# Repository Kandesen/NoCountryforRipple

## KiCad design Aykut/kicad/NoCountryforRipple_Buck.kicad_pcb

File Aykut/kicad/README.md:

# KiCad project: 60 W synchronous buck (LTC7801)

Open `NoCountryforRipple_Buck.kicad_pro` in KiCad 10. The files were generated with KiCad 7.0 tools, and KiCad 10 upgrades them when you save.

| File | Content |
|---|---|
| `NoCountryforRipple_Buck.kicad_sch` | Schematic (one A3 sheet): input + add-on 1, power stage, controller, add-on 2 |
| `NoCountryforRipple_Buck.kicad_pcb` | 4-layer PCB, 78 × 62 mm, fully routed |
| `lib/NCFR.kicad_sym` | Project symbols: `LTC7801` and `TLV431_DBZ` |
| `lib/NCFR.pretty/LTC7801_FE24_AA.kicad_mod` | LTC7801 TSSOP-24 footprint with exposed pad (FE24 AA: EP 2.74 × 3.25 mm, 6 thermal vias) |
| `bom/BOM_NoCountryforRipple_Buck.csv` | BOM grouped by MPN, with fit status, supplier to order from (EKOM / Özdisan / Mouser), stock and prices at each, and Digi-Key/Mouser search links |
| `docs/` | Schematic PDF, layer plots and `assembly_top.pdf` (part outlines with every reference, A4, for hand assembly) |

## Symbol fields
Every part has `MPN`, `Manufacturer` and `Fit`. `Fit` is one of: Base, Add-on 1 (reverse polarity), Add-on 2 (current limit), or a DNP option. DNP parts carry KiCad's *Do not populate* flag.
- **Removing add-on 1:** leave Q3, R1 and D1 unpopulated and fit JP1 (a 0 Ω 2512 resistor or a wire).
- **Removing add-on 2:** leave every part in the add-on 2 box unpopulated (U2–U4, D2, R15, R20–R28, C23, C25–C28, TP13).

## Board
- **Stack-up:** F.Cu (power copper + parts), In1.Cu (solid GND), In2.Cu (signals + GND fill), B.Cu (signals + GND fill). Standard 1.6 mm, 1 oz outer layers.
- **Rules:** minimum clearance 0.2 mm, minimum track 0.2 mm, vias 0.6/0.3 mm, 0.5 mm to the board edge. Every part is on the top side; there is no stencil, so paste is applied with the dispenser.
- **Power copper (F.Cu zones):** VIN, VIN_N (reverse-polarity FET), SW, SNSP (L1 → R5) and VOUT. The six input ceramics sit on the VIN/GND boundary directly above Q1 and Q2 (hot loop about 10 × 8 mm over the solid In1 GND).
- **Current sense:** Kelvin traces from inside the R5 pads run on In2 to R6/R7 (LTC7801 SENSE± filter) and on B.Cu to U2 (INA180).
- **Gate drive:** U1 → R2/R3 (0 Ω, change to a few Ω to slow the edges) → vias next to the Q1/Q2 gate pads. R2 sits directly above the gate-driver pins and R3 on the direct line towards Q2; test points TP4 (TG) and TP5 (BG) are next to them. Controller pin to MOSFET gate: TG about 29 mm (the straight line is 22 mm, because Q1 is at the far end of the power stage), BG about 21 mm. The TG track runs on In2 next to its SW return for most of its length. D3 (optional bootstrap diode, not fitted) was moved above the controller to make room for R3.
- **DRC (KiCad 7):** no clearance errors, no unconnected items. No silkscreen overlaps. The only remaining items are "library footprint" notices that only appear because the generator did not have your library paths.

## Sourcing
- **Supplier order:** e-komponent.com (EKOM, Digi-Key's distributor in Turkey) and Özdisan first; Digi-Key or Mouser (mouser.com.tr) only for parts neither of them stocks. Rule per BOM line: the exact part at EKOM → EKOM; otherwise the exact part at Özdisan → Özdisan; otherwise an equivalent (same footprint, pinout and rating) at EKOM/Özdisan; otherwise Mouser/Digi-Key. The BOM's "Order from / Order part" columns apply this; the EKOM, Özdisan and Mouser/Digi-Key columns list what each one had on **22 Nov 2026**.
- **EKOM:** most of its stock is Digi-Key stock shipped from abroad (7–10 working days, estimated dispatch 1–7 Dec 2026); the price includes shipping and customs. Only R25 (RC0805FR-0730K1L) was in stock in Turkey (1–3 days). Prices in the BOM are EKOM's 1-piece USD price without the 20 % VAT (the TL price on the site includes VAT).
- **What the BOM orders:** every part, including the ones not fitted by default (D3, JP1, R4, C13, R11), plus a limited set of spares that keeps the order under the 100 USD budget. "Qty per board" is the fitted quantity, "Spares" the extra pieces and "Qty to order" their sum.
- **Spares and why:** one LTC7801 (hardest part to hand-solder without a stencil, longest lead time); one BSC117N08NS5 (Q1/Q2 are the most likely to fail during bring-up); one LM2904B and one 1N4148W (cheap); one of every 0805 resistor and capacitor in a fitted position, once per part number (easily lost when hand-soldering). No spares for L1, R5, the 1206/1210 capacitors, C1, C10, Q3, U2, U4 or the parts not fitted by default.
- **Cost of the order (single-unit prices, USD excl. VAT):** base 61.6, add-on 1 4.1, add-on 2 5.5, parts not fitted by default 1.7, spares 22.7, total about 95.6. By supplier: EKOM 61.6, Özdisan 2.8 (estimated with Mouser prices; Royalohm resistors are sold in 100s), Mouser 31.2. Quantity breaks make the real total a little lower, but EKOM's USD prices follow the exchange rate, so recheck the total on the order day.
- **Every MPN in the schematic and BOM is the part that is ordered** (the "Order part" column says "same part" on every line). To get there, these design parts were replaced on 22 Nov 2026 by equivalents that EKOM/Özdisan stock (same footprint, pinout and rating):
  - C10: KEMET A768EB107M1ELAS036 (100 µF 25 V polymer, 6.3 mm can, 36 mΩ, 1.26 A ripple) instead of Panasonic EEH-ZA1E101XP.
  - C15: KEMET C0805C104K1RACTU; C20: KEMET C0805C682K5RACTU (instead of Yageo CC0805 parts).
  - U2: INA180A1IDBVT (same IC, industrial grade) instead of INA180A1QDBVRQ1. U4: TLV431BCDBZR (0–70 °C grade, same accuracy and pinout) instead of TLV431BIDBZR. D1: Taiwan Semiconductor BZT52C12-G RHG (12 V, 5 %) instead of Comchip BZT52B12-HF.
  - J1/J2 plug: Phoenix 1765551 (MSTB 2,5/2-ST-5,08 AU, same series) instead of 1757019, which EKOM only quotes. The header 1757242 is unchanged.
  - R14: Royalohm 0805S8F2372T5E from Özdisan (sold in 100s) instead of Yageo RC0805FR-0723K7L. R4 (not fitted): Yageo RC1206JR-072R2L (5 %) instead of the 1 % part.
- **Alternative R28 values** (not fitted, two of each): 2.37 kΩ (7.94 A, EKOM), 2.32 kΩ (7.80 A, Özdisan), 2.26 kΩ (7.64 A, Özdisan), 2.21 kΩ (7.50 A, EKOM) and 1.54 kΩ (5.53 A, Özdisan; the standard 5 A design if the overload bonus is dropped). R28 = 2.49 kΩ (8.26 A) is fitted for the first power-up so that 12 V / 7.5 A is always supplied in regulation, even with worst-case tolerances (about ±6 %). After the real limit has been measured on the bench, R28 is swapped to bring the limit to about 7.6 A (2 % above the 7.5 A target).
- **From Mouser (mouser.com.tr):** U1 LTC7801EFE#PBF × 2 (EKOM lists only the LTC7801IFE#PBF, on request; Mouser Türkiye had 1,587), R12 1.02 MΩ, D3 BAT46ZFILM (no BAT46 in stock at EKOM) and JP1 CRF2512-J/-000ELF.
- **L1 (Würth 74435582200):** EKOM 101 (Digi-Key stock), 9.18 USD; Mouser 0 (3,543 due 11 Dec 2026). Order it first.
- **Parts not fitted by default** are ordered too: R4, C13 and R11 (EKOM), D3 and JP1 (Mouser). EKOM's Bourns CRF2512-JZ-R005ELF (5 mΩ metal strip) would also work for JP1 (48 mW at 3.1 A).
- Earlier swaps re-checked at EKOM: Murata GRM32ER72A225KA35L, Samsung CL32B226KAJNNNE / CL31B106KAHNNNE / CL21B104KCFNNNE and BAT46W-7-F are out of stock there; Yageo RC2512JK-070RL is stocked but rated 2 A (too low for JP1); INA180B1IDBVR is stocked but has the other pinout. None of the earlier swaps needs to be undone.

## What has been verified
- **Schematic ↔ intended design:** KiCad's exported netlist was compared pin by pin with the intended netlist (191 pins, no differences). The intended netlist was reviewed net by net against the design.
- **Pinouts checked against datasheets:**
  - LTC7801 FE24: pin table; exposed pad = GND.
  - INA180A1 (pinout A): OUT 1, GND 2, IN+ 3, IN− 4, VS 5.
  - TLV431 DBZ: 1 REF, 2 K, 3 A (custom symbol).
  - BSC117N08NS5 / BSC030N08NS5 (TDSON-8): 1–3 S, 4 G, 5 D.
  - Polarity of the polymer capacitors C1 and C10.
- **Simulation ↔ schematic:** the LTspice files in `sim/ltspice/` use the same reference designators and values as this schematic (lumped parts: C2_12 = C2–C5, C11, C12; C6_9 = C6–C9). The report figures and the BOM notes use the same names; RB/RA/RS/RC/CC/CC2 in the report's equations are R8/R9/R5/R16/C20/C21.
- **Board ↔ schematic:** every footprint is linked to its symbol, and all pad nets match the netlist (no differences).
- **DRC (KiCad 7.0.11):** no clearance errors, no unconnected items.
- **Copper continuity:** the VIN, VIN_N, SW, SNSP and VOUT copper each fill as one island. In1, In2 and B.Cu GND are each one island.
- **Kelvin sensing:** the sense traces from inside the R5 pads connect only to R6/R7 and U2. No other VOUT/SNSP copper touches them, so no load current flows in the sense lines.
- **Cost:** about 71 USD (excl. VAT) for one fully populated board (base 61.6, add-on 1 4.1, add-on 2 5.5); about 95.6 USD for the whole order with the parts not fitted by default and the spares. See the BOM totals.

## Known points to improve or check interactively
- **Gate drive and ringing:** the gate paths were shortened on 22 Nov (TG about 34 → 29 mm, BG 28 → 21 mm). If the switch node rings too much on the bench (TP3, 48 V, full load), first increase R2/R3 to 2.2–4.7 Ω, then fit the R4/C13 snubber (2.2 Ω, 330 pF C0G; R4 dissipates about 0.15 W at 48 V).
- **Decoupling at U1:** C16 (DRVCC, 10 µF) now sits left of the controller with about 4 mm of track to pins 17/18 (was about 10 mm), and C15 (VIN, 100 nF) about 4 mm from pin 19 (was 7.6 mm). Moved on 22 Nov; DRC clean.
- **Silkscreen:** every label is placed clear of pads and other labels. Six small parts next to the controller (C15, C19, C20, C21, C28, R19) had no free space for a label, so their labels are hidden on the board; `docs/assembly_top.pdf` shows all references.
- **Vias in the R5 pads:** the Kelvin vias sit inside R5's pads, so a little solder may wick into them. Use enough paste on R5.

## Before ordering (in KiCad 10)
1. Run ERC on the schematic. KiCad 7's command line has no ERC, so connectivity was checked instead by comparing the exported netlist pin by pin with the intended netlist.
2. Run *Tools → Update PCB from Schematic*. Nothing should change, because the footprints are linked to their symbols.
3. Refill zones (B), run DRC, and look at the 3D view.
4. Check the LTC7801 footprint against the datasheet's FE24(AA) drawing (exposed-pad size), and that the 5.08 mm header faces outward.
5. Ask the PCB manufacturer for its 4-layer stack-up and minimum rules (most allow 0.15 mm / 0.3 mm drill), then plot the Gerbers and drill files.

## Report names → KiCad designators
| Report | KiCad | | Report | KiCad |
|---|---|---|---|---|
| R_S (6 mΩ sense) | R5 | | R_SS (330 k) | R15 |
| R_A / R_B (feedback) | R9 / R8 | | R_inj (22 k) | R23 |
| R_C / C_C / C_C2 (ITH) | R16 / C20 / C21 | | R_i / C_i (integrator) | R22 / C26 |
| C_SS | C19 | | R_2 / C_2 (integrator input) | R21 / C25 |
| R_FREQ / R_DRVSET | R17 / R18 | | UVLO divider | R12, R13, R14 |
| Input ceramics | C2–C5, C11, C12 | | Output ceramics / polymer | C6–C9 / C10 |

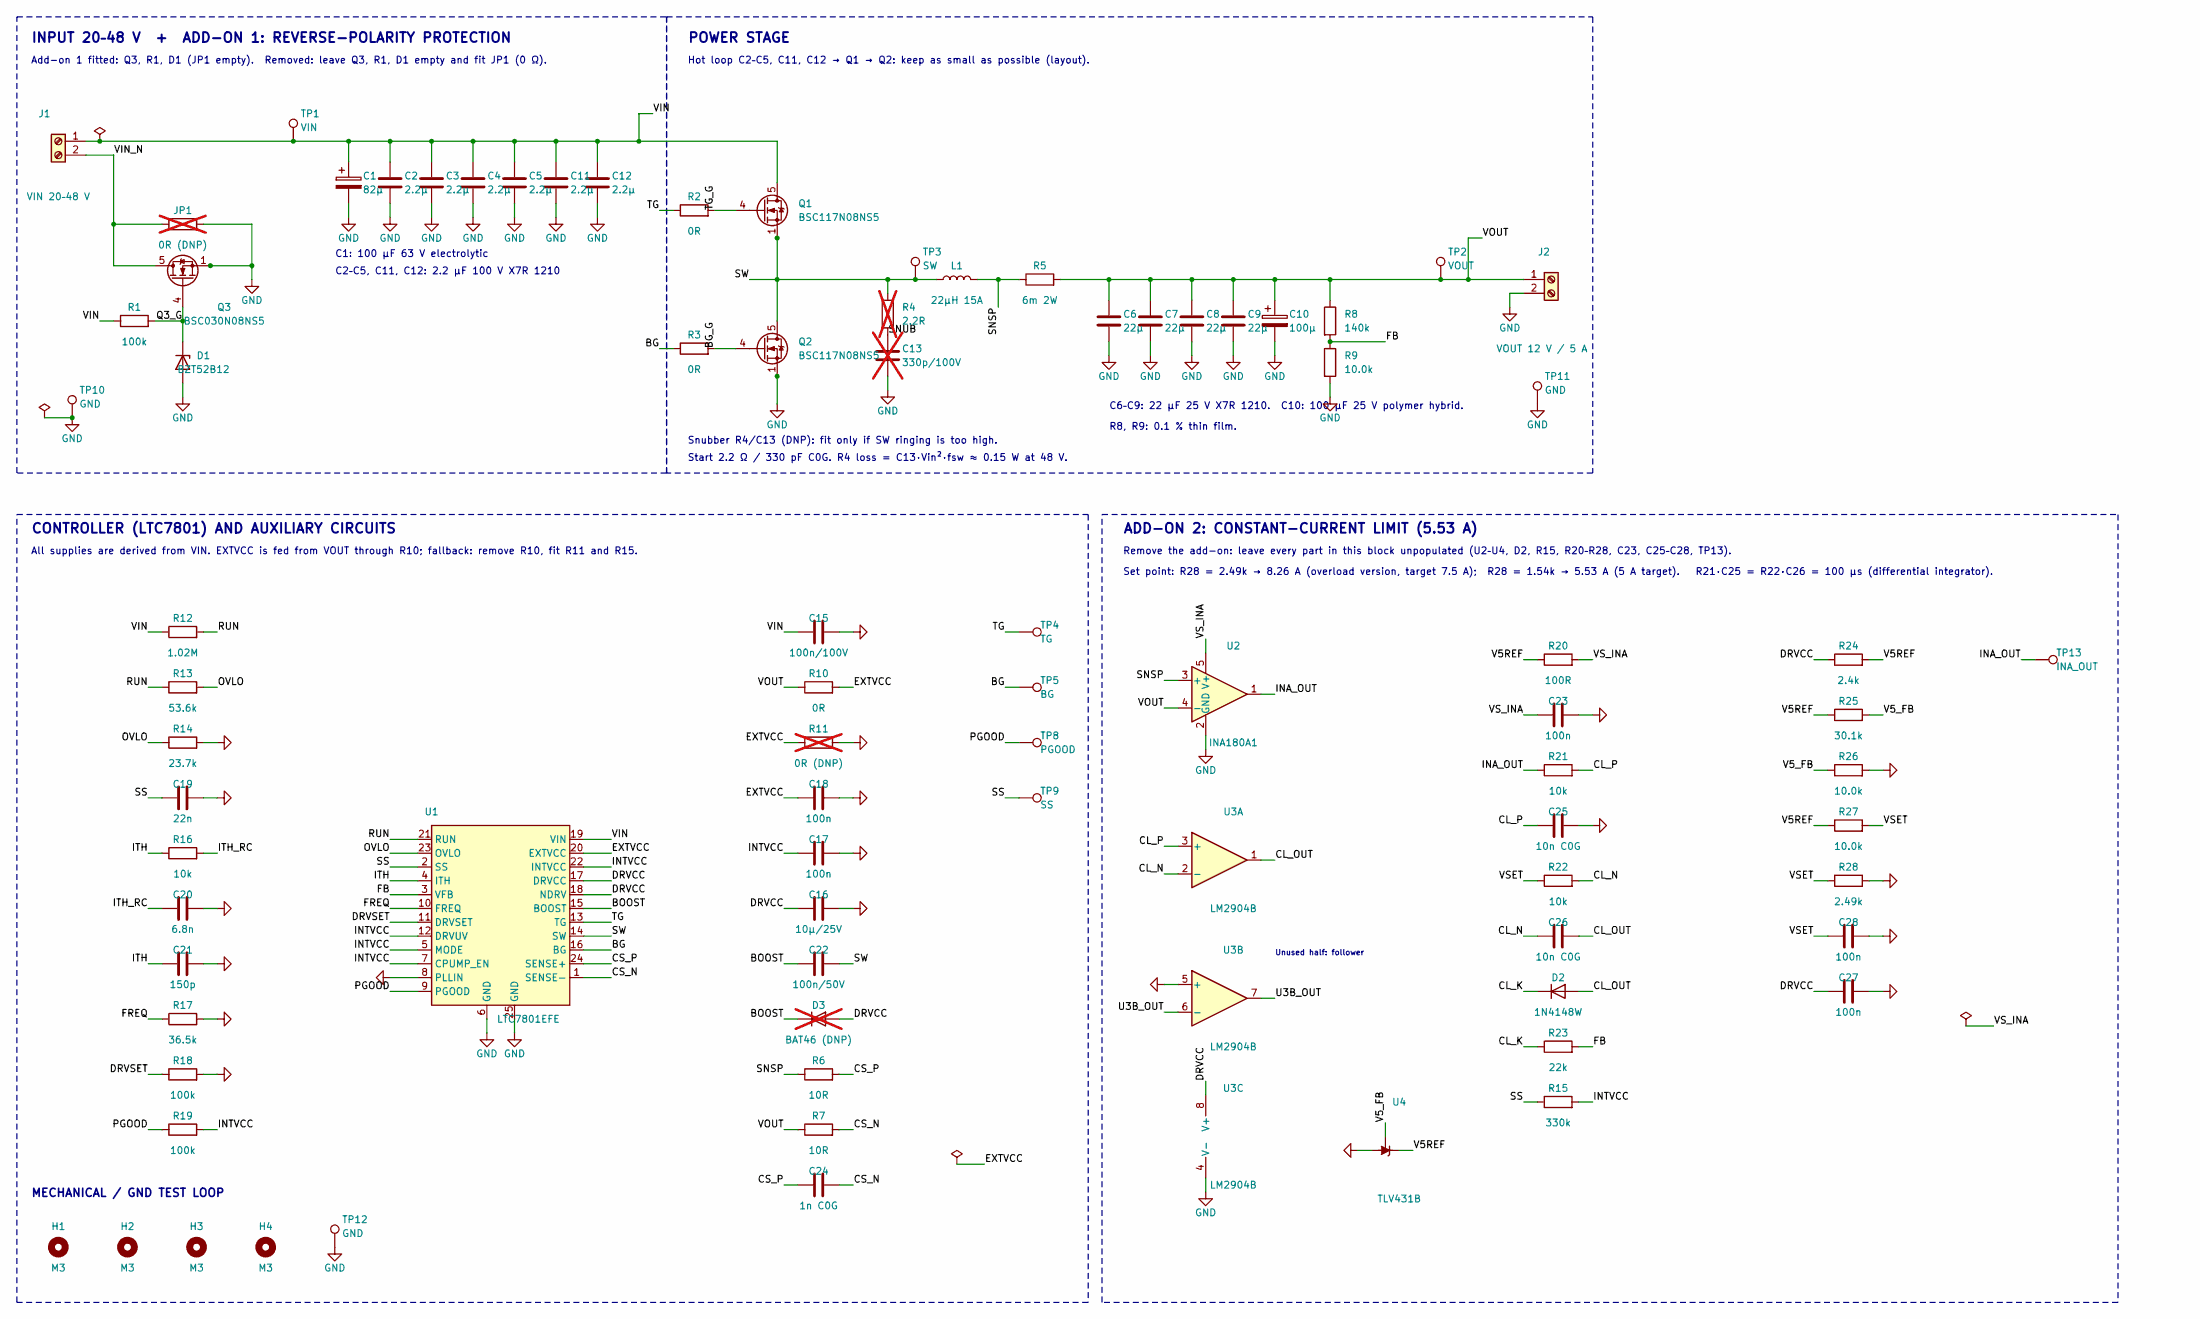
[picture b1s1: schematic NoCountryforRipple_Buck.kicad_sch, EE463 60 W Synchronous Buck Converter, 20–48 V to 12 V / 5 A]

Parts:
C1: 82µ; CP_Elec_10x10; Voltage 63 V; MPN A786MN826M1JLAS018
C2, C3, C4, C5, C11, C12: 2.2µ; C_1210_3225Metric; Voltage 100 V; MPN C1210C225K1RACTU
C6, C7, C8, C9: 22µ; C_1210_3225Metric; Voltage 25 V; MPN C3225X7R1E226M250AB
C10: 100µ; CP_Elec_6.3x7.7; Voltage 25 V; MPN EEH-ZA1E101XP
C13: 330p/100V; C_0805_2012Metric; MPN C0805C331J1GACTU; not fitted
C15: 100n/100V; C_0805_2012Metric; MPN CC0805KKX7R0BB104
C16: 10µ/25V; C_1206_3216Metric; MPN CC1206KKX7R8BB106
C17, C18, C23, C27, C28: 100n; C_0805_2012Metric; MPN CL21B104KBCNNNC
C19: 22n; C_0805_2012Metric; MPN CL21B223KBANNNC
C20: 6.8n; C_0805_2012Metric; MPN CC0805KRX7R9BB682
C21: 150p; C_0805_2012Metric; MPN CC0805JRNPO9BN151
C22: 100n/50V; C_0805_2012Metric; MPN CL21B104KBCNNNC
C24: 1n C0G; C_0805_2012Metric; MPN CC0805JRNPO9BN102
C25, C26: 10n C0G; C_0805_2012Metric; MPN CL21C103JBFNNNE
D1: BZT52B12; D_SOD-123; MPN BZT52B12-HF
D2: 1N4148W; D_SOD-123; MPN 1N4148W-7-F
D3: BAT46 (DNP); D_SOD-123; MPN BAT46ZFILM; not fitted
H1, H2, H3, H4: M3; MountingHole_3.2mm_M3; MPN —
J1: VIN 20–48 V; PhoenixContact_MSTBA_2,5_2-G-5,08_1x02_P5.08mm_Horizontal; MPN 1757242 + plug 1757019
J2: VOUT 12 V / 5 A; PhoenixContact_MSTBA_2,5_2-G-5,08_1x02_P5.08mm_Horizontal; MPN 1757242 + plug 1757019
JP1: 0R (DNP); R_2512_6332Metric; MPN CRF2512-J/-000ELF; not fitted
L1: 22µH 15A; L_Wuerth_HCI-2212; MPN 74435582200
Q1, Q2: BSC117N08NS5; TDSON-8-1; MPN BSC117N08NS5ATMA1
Q3: BSC030N08NS5; TDSON-8-1; MPN BSC030N08NS5ATMA1
R1, R18, R19: 100k; R_0805_2012Metric; MPN RC0805FR-07100KL
R2, R3, R10: 0R; R_0805_2012Metric; MPN RC0805JR-070RL
R4: 2.2R; R_1206_3216Metric; MPN RC1206FR-072R2L; not fitted
R5: 6m 2W; R_2512_6332Metric; MPN PA2512FKF7W0R006E
R6, R7: 10R; R_0805_2012Metric; MPN RC0805FR-0710RL
R8: 140k; R_0805_2012Metric; MPN RT0805BRD07140KL
R9: 10.0k; R_0805_2012Metric; MPN RT0805BRD0710KL
R11: 0R (DNP); R_0805_2012Metric; MPN RC0805JR-070RL; not fitted
R12: 1.02M; R_0805_2012Metric; MPN RC0805FR-071M02L
R13: 53.6k; R_0805_2012Metric; MPN RC0805FR-0753K6L
R14: 23.7k; R_0805_2012Metric; MPN RC0805FR-0723K7L
R15: 330k; R_0805_2012Metric; MPN RC0805FR-07330KL
R16, R21, R22: 10k; R_0805_2012Metric; MPN RC0805FR-0710KL
R17: 36.5k; R_0805_2012Metric; MPN RC0805FR-0736K5L
R20: 100R; R_0805_2012Metric; MPN RC0805FR-07100RL
R23: 22k; R_0805_2012Metric; MPN RC0805FR-0722KL
R24: 2.4k; R_0805_2012Metric; MPN RC0805FR-072K4L
R25: 30.1k; R_0805_2012Metric; MPN RC0805FR-0730K1L
R26, R27: 10.0k; R_0805_2012Metric; MPN RC0805FR-0710KL
R28: 2.49k; R_0805_2012Metric; MPN RC0805FR-072K49L
TP1: VIN; TestPoint_Pad_D2.0mm; MPN —
TP2: VOUT; TestPoint_Pad_D2.0mm; MPN —
TP3: SW; TestPoint_Pad_D1.5mm; MPN —
TP4: TG; TestPoint_Pad_D1.5mm; MPN —
TP5: BG; TestPoint_Pad_D1.5mm; MPN —
TP8: PGOOD; TestPoint_Pad_D1.5mm; MPN —
TP9: SS; TestPoint_Pad_D1.5mm; MPN —
TP10, TP11, TP12: GND; TestPoint_Loop_D2.50mm_Drill1.0mm; MPN —
TP13: INA_OUT; TestPoint_Pad_D1.5mm; MPN —
U1: LTC7801EFE; LTC7801_FE24_AA; MPN LTC7801EFE#PBF
U2: INA180A1; SOT-23-5; MPN INA180A1QDBVRQ1
U3: LM2904B; SOIC-8_3.9x4.9mm_P1.27mm; MPN LM2904BIDR
U4: TLV431B; SOT-23; MPN TLV431BIDBZR

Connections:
BG: R3.1, TP5.1, U1.16 (BG)
BG_G: Q2.4 (G), R3.2
BOOST: C22.1, D3.1 (K), U1.15 (BOOST)
CL_K: D2.1 (K), R23.1
CL_N: C26.1, R22.2, U3.2 (-)
CL_OUT: C26.2, D2.2 (A), U3.1
CL_P: C25.1, R21.2, U3.3 (+)
CS_N: C24.2, R7.2, U1.1 (SENSE-)
CS_P: C24.1, R6.2, U1.24 (SENSE+)
DRVCC: C16.1, C27.1, D3.2 (A), R24.1, U1.17 (DRVCC), U1.18 (NDRV), U3.8 (V+)
DRVSET: R18.1, U1.11 (DRVSET)
EXTVCC: C18.1, R10.2, R11.1, U1.20 (EXTVCC)
FB: R8.2, R9.1, R23.2, U1.3 (VFB)
FREQ: R17.1, U1.10 (FREQ)
GND: C1.2, C2.2, C3.2, C4.2, C5.2, C6.2, C7.2, C8.2, C9.2, C10.2, C11.2, C12.2, C13.2, C15.2, C16.2, C17.2, C18.2, C19.2, C20.2, C21.2, C23.2, C25.2, C27.2, C28.2, D1.2 (A), J2.2, JP1.2, Q2.1 (S), Q2.2 (S), Q2.3 (S), Q3.1 (S), Q3.2 (S), Q3.3 (S), R9.2, R11.2, R14.2, R17.2, R18.2, R26.2, R28.2, TP10.1, TP11.1, TP12.1, U1.6 (GND), U1.8 (PLLIN), U1.25 (GND), U2.2 (GND), U3.4 (V-), U3.5 (+), U4.3 (A)
INA_OUT: R21.1, TP13.1, U2.1
INTVCC: C17.1, R15.2, R19.2, U1.5 (MODE), U1.7 (CPUMP_EN), U1.12 (DRVUV), U1.22 (INTVCC)
ITH: C21.1, R16.1, U1.4 (ITH)
ITH_RC: C20.1, R16.2
OVLO: R13.2, R14.1, U1.23 (OVLO)
PGOOD: R19.1, TP8.1, U1.9 (PGOOD)
Q3_G: D1.1 (K), Q3.4 (G), R1.2
RUN: R12.2, R13.1, U1.21 (RUN)
SNSP: L1.2, R5.1, R6.1, U2.3 (+)
SNUB: C13.1, R4.2
SS: C19.1, R15.1, TP9.1, U1.2 (SS)
SW: C22.2, L1.1, Q1.1 (S), Q1.2 (S), Q1.3 (S), Q2.5 (D), R4.1, TP3.1, U1.14 (SW)
TG: R2.1, TP4.1, U1.13 (TG)
TG_G: Q1.4 (G), R2.2
U3B_OUT: U3.6 (-), U3.7
V5REF: R20.1, R24.2, R25.1, R27.1, U4.2 (K)
V5_FB: R25.2, R26.1, U4.1 (REF)
VIN: C1.1, C2.1, C3.1, C4.1, C5.1, C11.1, C12.1, C15.1, J1.1, Q1.5 (D), R1.1, R12.1, TP1.1, U1.19 (VIN)
VIN_N: J1.2, JP1.1, Q3.5 (D)
VOUT: C6.1, C7.1, C8.1, C9.1, C10.1, J2.1, R5.2, R7.1, R8.1, R10.1, TP2.1, U2.4 (-)
VSET: C28.1, R22.1, R27.2, R28.1
VS_INA: C23.1, R20.2, U2.5 (V+)

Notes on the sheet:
INPUT 20–48 V + ADD-ON 1: REVERSE-POLARITY PROTECTION
Add-on 1 fitted: Q3, R1, D1 (JP1 empty). Removed: leave Q3, R1, D1 empty and fit JP1 (0 Ω).
C1: 100 µF 63 V electrolytic
C2–C5, C11, C12: 2.2 µF 100 V X7R 1210
Snubber R4/C13 (DNP): fit only if SW ringing is too high.
Start 2.2 Ω / 330 pF C0G. R4 loss = C13·Vin²·fsw ≈ 0.15 W at 48 V.
POWER STAGE
Hot loop C2–C5, C11, C12 → Q1 → Q2: keep as small as possible (layout).
C6–C9: 22 µF 25 V X7R 1210. C10: 100 µF 25 V polymer hybrid.
R8, R9: 0.1 % thin film.
CONTROLLER (LTC7801) AND AUXILIARY CIRCUITS
All supplies are derived from VIN. EXTVCC is fed from VOUT through R10; fallback: remove R10, fit R11 and R15.
ADD-ON 2: CONSTANT-CURRENT LIMIT (5.53 A)
Remove the add-on: leave every part in this block unpopulated (U2–U4, D2, R15, R20–R28, C23, C25–C28, TP13).
Set point: R28 = 2.49k → 8.26 A (overload version, target 7.5 A); R28 = 1.54k → 5.53 A (5 A target). R21·C25 = R22·C26 = 100 µs (differential integrator).
Unused half: follower
MECHANICAL / GND TEST LOOP

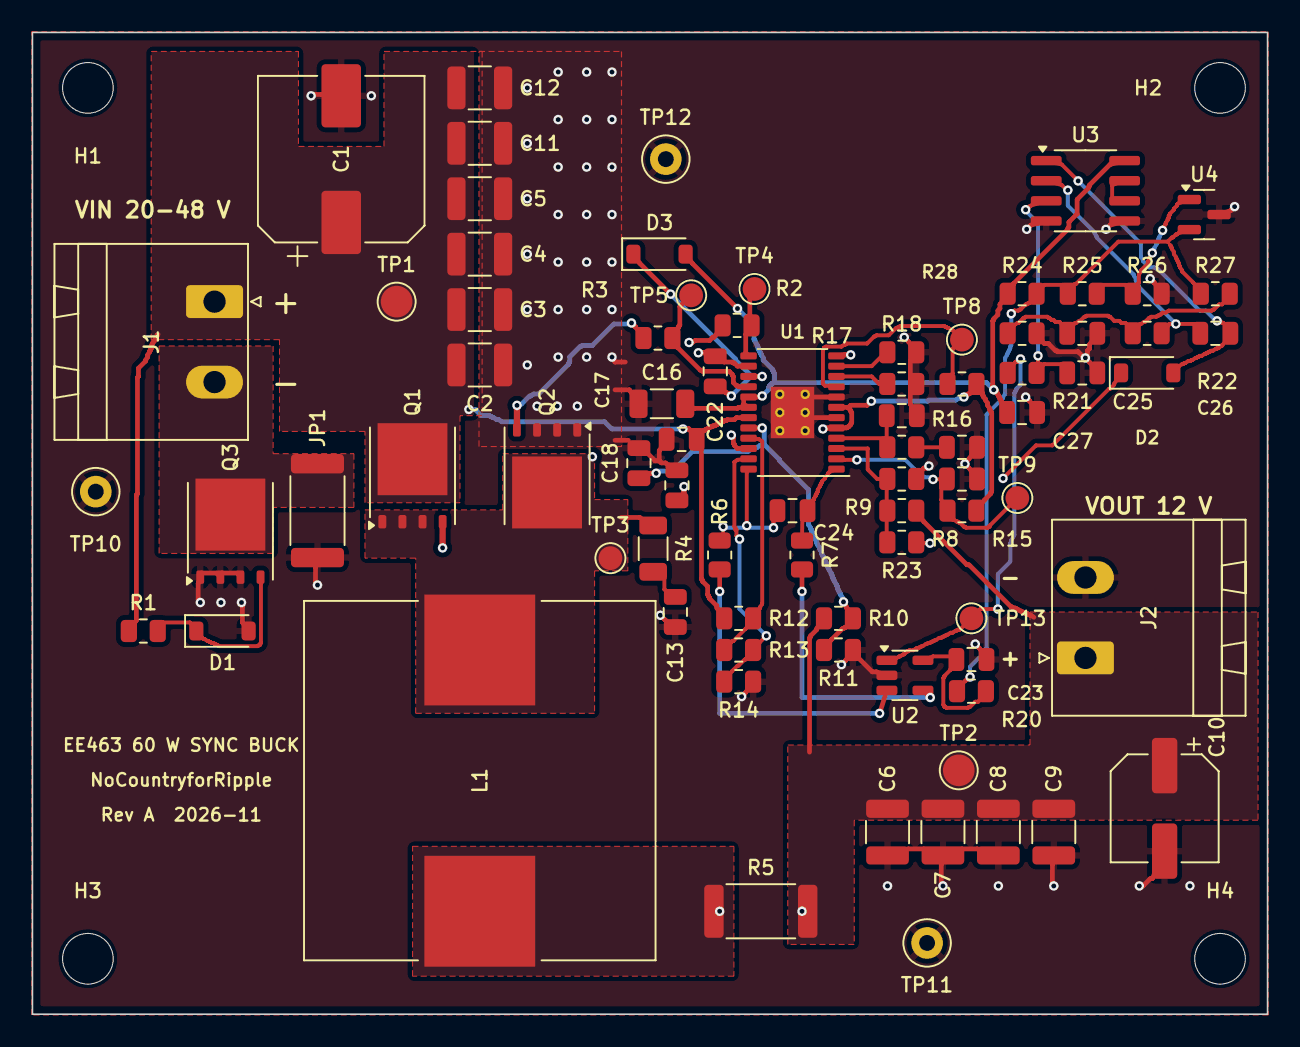
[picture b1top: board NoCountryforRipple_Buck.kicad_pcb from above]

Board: 4 copper layers, 78.0 x 62.0 mm, 84 parts (0 on the bottom side), 37 nets.
